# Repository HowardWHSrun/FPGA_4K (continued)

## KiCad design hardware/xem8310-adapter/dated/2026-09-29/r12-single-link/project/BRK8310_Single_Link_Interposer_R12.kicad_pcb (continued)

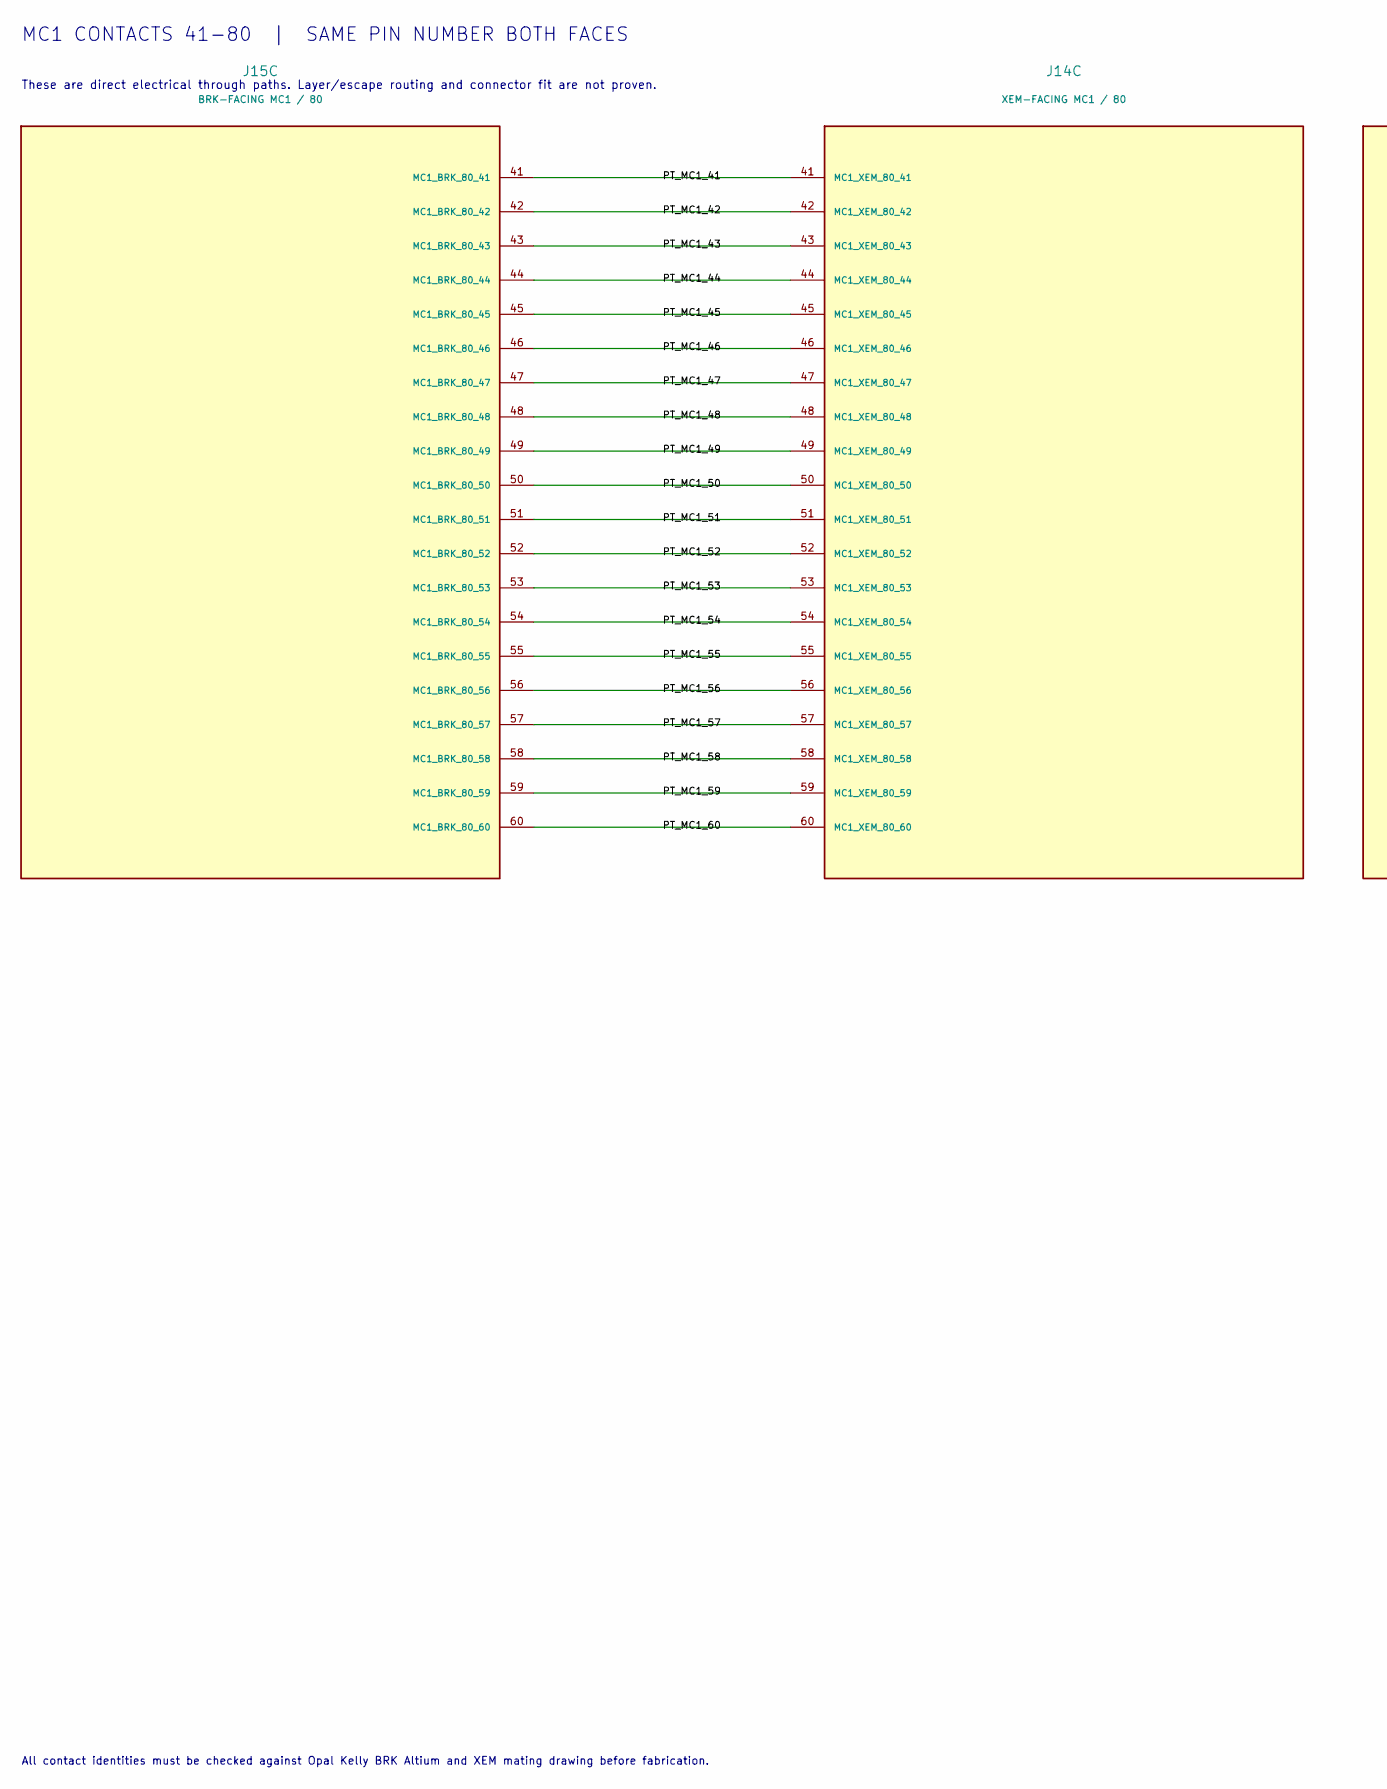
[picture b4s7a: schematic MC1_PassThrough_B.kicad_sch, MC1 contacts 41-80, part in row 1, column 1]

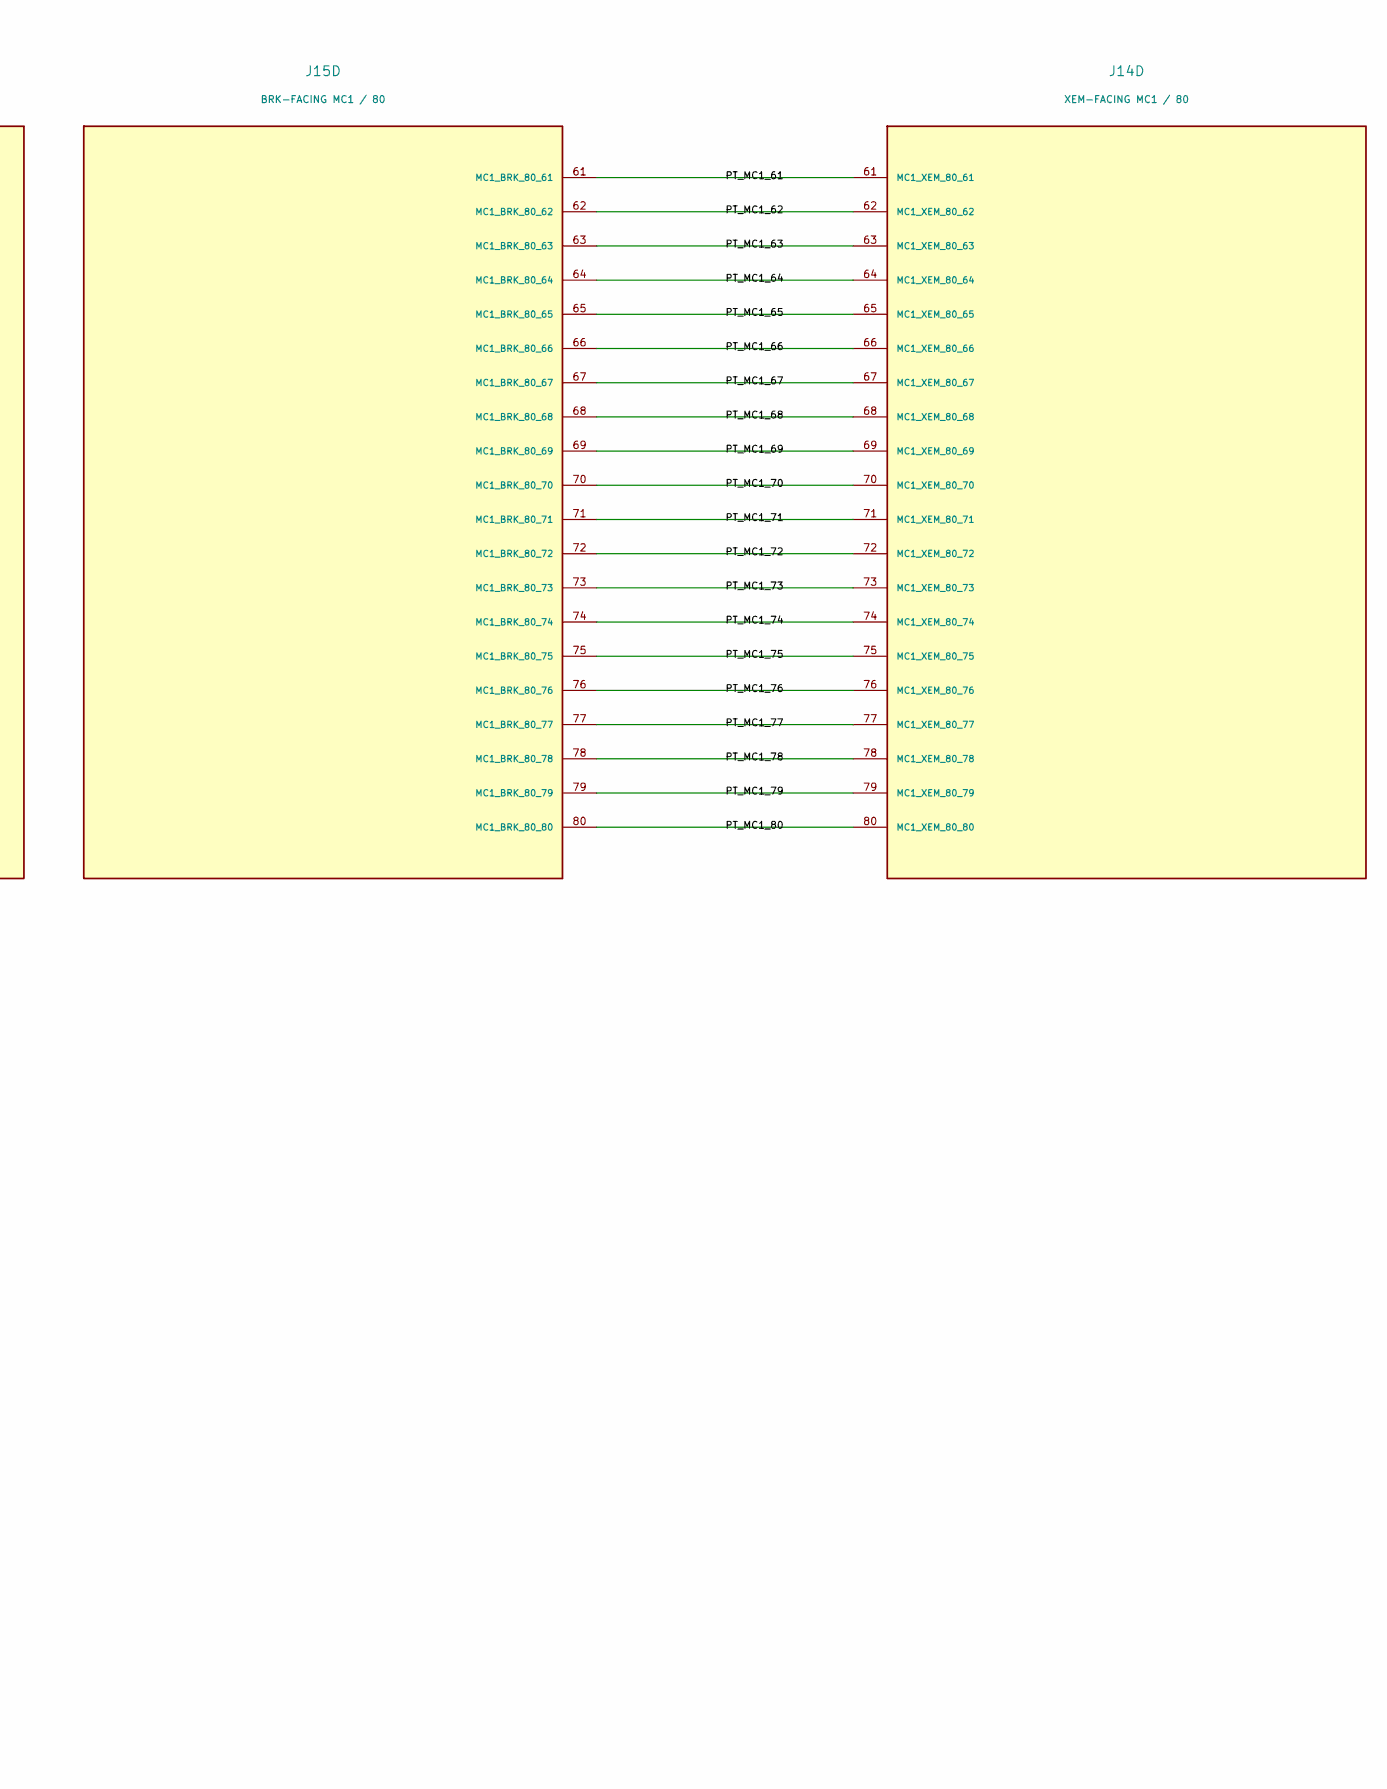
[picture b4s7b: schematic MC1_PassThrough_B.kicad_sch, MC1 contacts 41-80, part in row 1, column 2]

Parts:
J14: XEM-FACING MC1 / 80; BTE_040_01_Top_OpalKelly
J15: BRK-FACING MC1 / 80; BSE_040_01_Bottom_SamtecDrawing

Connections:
/07 / MC1 41-80 PASS-THROUGH/PT_MC1_41: J14.41 (MC1_XEM_80_41), J15.41 (MC1_BRK_80_41)
/07 / MC1 41-80 PASS-THROUGH/PT_MC1_42: J14.42 (MC1_XEM_80_42), J15.42 (MC1_BRK_80_42)
/07 / MC1 41-80 PASS-THROUGH/PT_MC1_43: J14.43 (MC1_XEM_80_43), J15.43 (MC1_BRK_80_43)
/07 / MC1 41-80 PASS-THROUGH/PT_MC1_44: J14.44 (MC1_XEM_80_44), J15.44 (MC1_BRK_80_44)
/07 / MC1 41-80 PASS-THROUGH/PT_MC1_45: J14.45 (MC1_XEM_80_45), J15.45 (MC1_BRK_80_45)
/07 / MC1 41-80 PASS-THROUGH/PT_MC1_46: J14.46 (MC1_XEM_80_46), J15.46 (MC1_BRK_80_46)
/07 / MC1 41-80 PASS-THROUGH/PT_MC1_47: J14.47 (MC1_XEM_80_47), J15.47 (MC1_BRK_80_47)
/07 / MC1 41-80 PASS-THROUGH/PT_MC1_48: J14.48 (MC1_XEM_80_48), J15.48 (MC1_BRK_80_48)
/07 / MC1 41-80 PASS-THROUGH/PT_MC1_49: J14.49 (MC1_XEM_80_49), J15.49 (MC1_BRK_80_49)
/07 / MC1 41-80 PASS-THROUGH/PT_MC1_50: J14.50 (MC1_XEM_80_50), J15.50 (MC1_BRK_80_50)
/07 / MC1 41-80 PASS-THROUGH/PT_MC1_51: J14.51 (MC1_XEM_80_51), J15.51 (MC1_BRK_80_51)
/07 / MC1 41-80 PASS-THROUGH/PT_MC1_52: J14.52 (MC1_XEM_80_52), J15.52 (MC1_BRK_80_52)
/07 / MC1 41-80 PASS-THROUGH/PT_MC1_53: J14.53 (MC1_XEM_80_53), J15.53 (MC1_BRK_80_53)
/07 / MC1 41-80 PASS-THROUGH/PT_MC1_54: J14.54 (MC1_XEM_80_54), J15.54 (MC1_BRK_80_54)
/07 / MC1 41-80 PASS-THROUGH/PT_MC1_55: J14.55 (MC1_XEM_80_55), J15.55 (MC1_BRK_80_55)
/07 / MC1 41-80 PASS-THROUGH/PT_MC1_56: J14.56 (MC1_XEM_80_56), J15.56 (MC1_BRK_80_56)
/07 / MC1 41-80 PASS-THROUGH/PT_MC1_57: J14.57 (MC1_XEM_80_57), J15.57 (MC1_BRK_80_57)
/07 / MC1 41-80 PASS-THROUGH/PT_MC1_58: J14.58 (MC1_XEM_80_58), J15.58 (MC1_BRK_80_58)
/07 / MC1 41-80 PASS-THROUGH/PT_MC1_59: J14.59 (MC1_XEM_80_59), J15.59 (MC1_BRK_80_59)
/07 / MC1 41-80 PASS-THROUGH/PT_MC1_60: J14.60 (MC1_XEM_80_60), J15.60 (MC1_BRK_80_60)
/07 / MC1 41-80 PASS-THROUGH/PT_MC1_61: J14.61 (MC1_XEM_80_61), J15.61 (MC1_BRK_80_61)
/07 / MC1 41-80 PASS-THROUGH/PT_MC1_62: J14.62 (MC1_XEM_80_62), J15.62 (MC1_BRK_80_62)
/07 / MC1 41-80 PASS-THROUGH/PT_MC1_63: J14.63 (MC1_XEM_80_63), J15.63 (MC1_BRK_80_63)
/07 / MC1 41-80 PASS-THROUGH/PT_MC1_64: J14.64 (MC1_XEM_80_64), J15.64 (MC1_BRK_80_64)
/07 / MC1 41-80 PASS-THROUGH/PT_MC1_65: J14.65 (MC1_XEM_80_65), J15.65 (MC1_BRK_80_65)
/07 / MC1 41-80 PASS-THROUGH/PT_MC1_66: J14.66 (MC1_XEM_80_66), J15.66 (MC1_BRK_80_66)
/07 / MC1 41-80 PASS-THROUGH/PT_MC1_67: J14.67 (MC1_XEM_80_67), J15.67 (MC1_BRK_80_67)
/07 / MC1 41-80 PASS-THROUGH/PT_MC1_68: J14.68 (MC1_XEM_80_68), J15.68 (MC1_BRK_80_68)
/07 / MC1 41-80 PASS-THROUGH/PT_MC1_69: J14.69 (MC1_XEM_80_69), J15.69 (MC1_BRK_80_69)
/07 / MC1 41-80 PASS-THROUGH/PT_MC1_70: J14.70 (MC1_XEM_80_70), J15.70 (MC1_BRK_80_70)
/07 / MC1 41-80 PASS-THROUGH/PT_MC1_71: J14.71 (MC1_XEM_80_71), J15.71 (MC1_BRK_80_71)
/07 / MC1 41-80 PASS-THROUGH/PT_MC1_72: J14.72 (MC1_XEM_80_72), J15.72 (MC1_BRK_80_72)
/07 / MC1 41-80 PASS-THROUGH/PT_MC1_73: J14.73 (MC1_XEM_80_73), J15.73 (MC1_BRK_80_73)
/07 / MC1 41-80 PASS-THROUGH/PT_MC1_74: J14.74 (MC1_XEM_80_74), J15.74 (MC1_BRK_80_74)
/07 / MC1 41-80 PASS-THROUGH/PT_MC1_75: J14.75 (MC1_XEM_80_75), J15.75 (MC1_BRK_80_75)
/07 / MC1 41-80 PASS-THROUGH/PT_MC1_76: J14.76 (MC1_XEM_80_76), J15.76 (MC1_BRK_80_76)
/07 / MC1 41-80 PASS-THROUGH/PT_MC1_77: J14.77 (MC1_XEM_80_77), J15.77 (MC1_BRK_80_77)
/07 / MC1 41-80 PASS-THROUGH/PT_MC1_78: J14.78 (MC1_XEM_80_78), J15.78 (MC1_BRK_80_78)
/07 / MC1 41-80 PASS-THROUGH/PT_MC1_79: J14.79 (MC1_XEM_80_79), J15.79 (MC1_BRK_80_79)
/07 / MC1 41-80 PASS-THROUGH/PT_MC1_80: J14.80 (MC1_XEM_80_80), J15.80 (MC1_BRK_80_80)

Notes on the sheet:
MC1 CONTACTS 41-80 | SAME PIN NUMBER BOTH FACES
These are direct electrical through paths. Layer/escape routing and connector fit are not proven.
All contact identities must be checked against Opal Kelly BRK Altium and XEM mating drawing before fabrication.

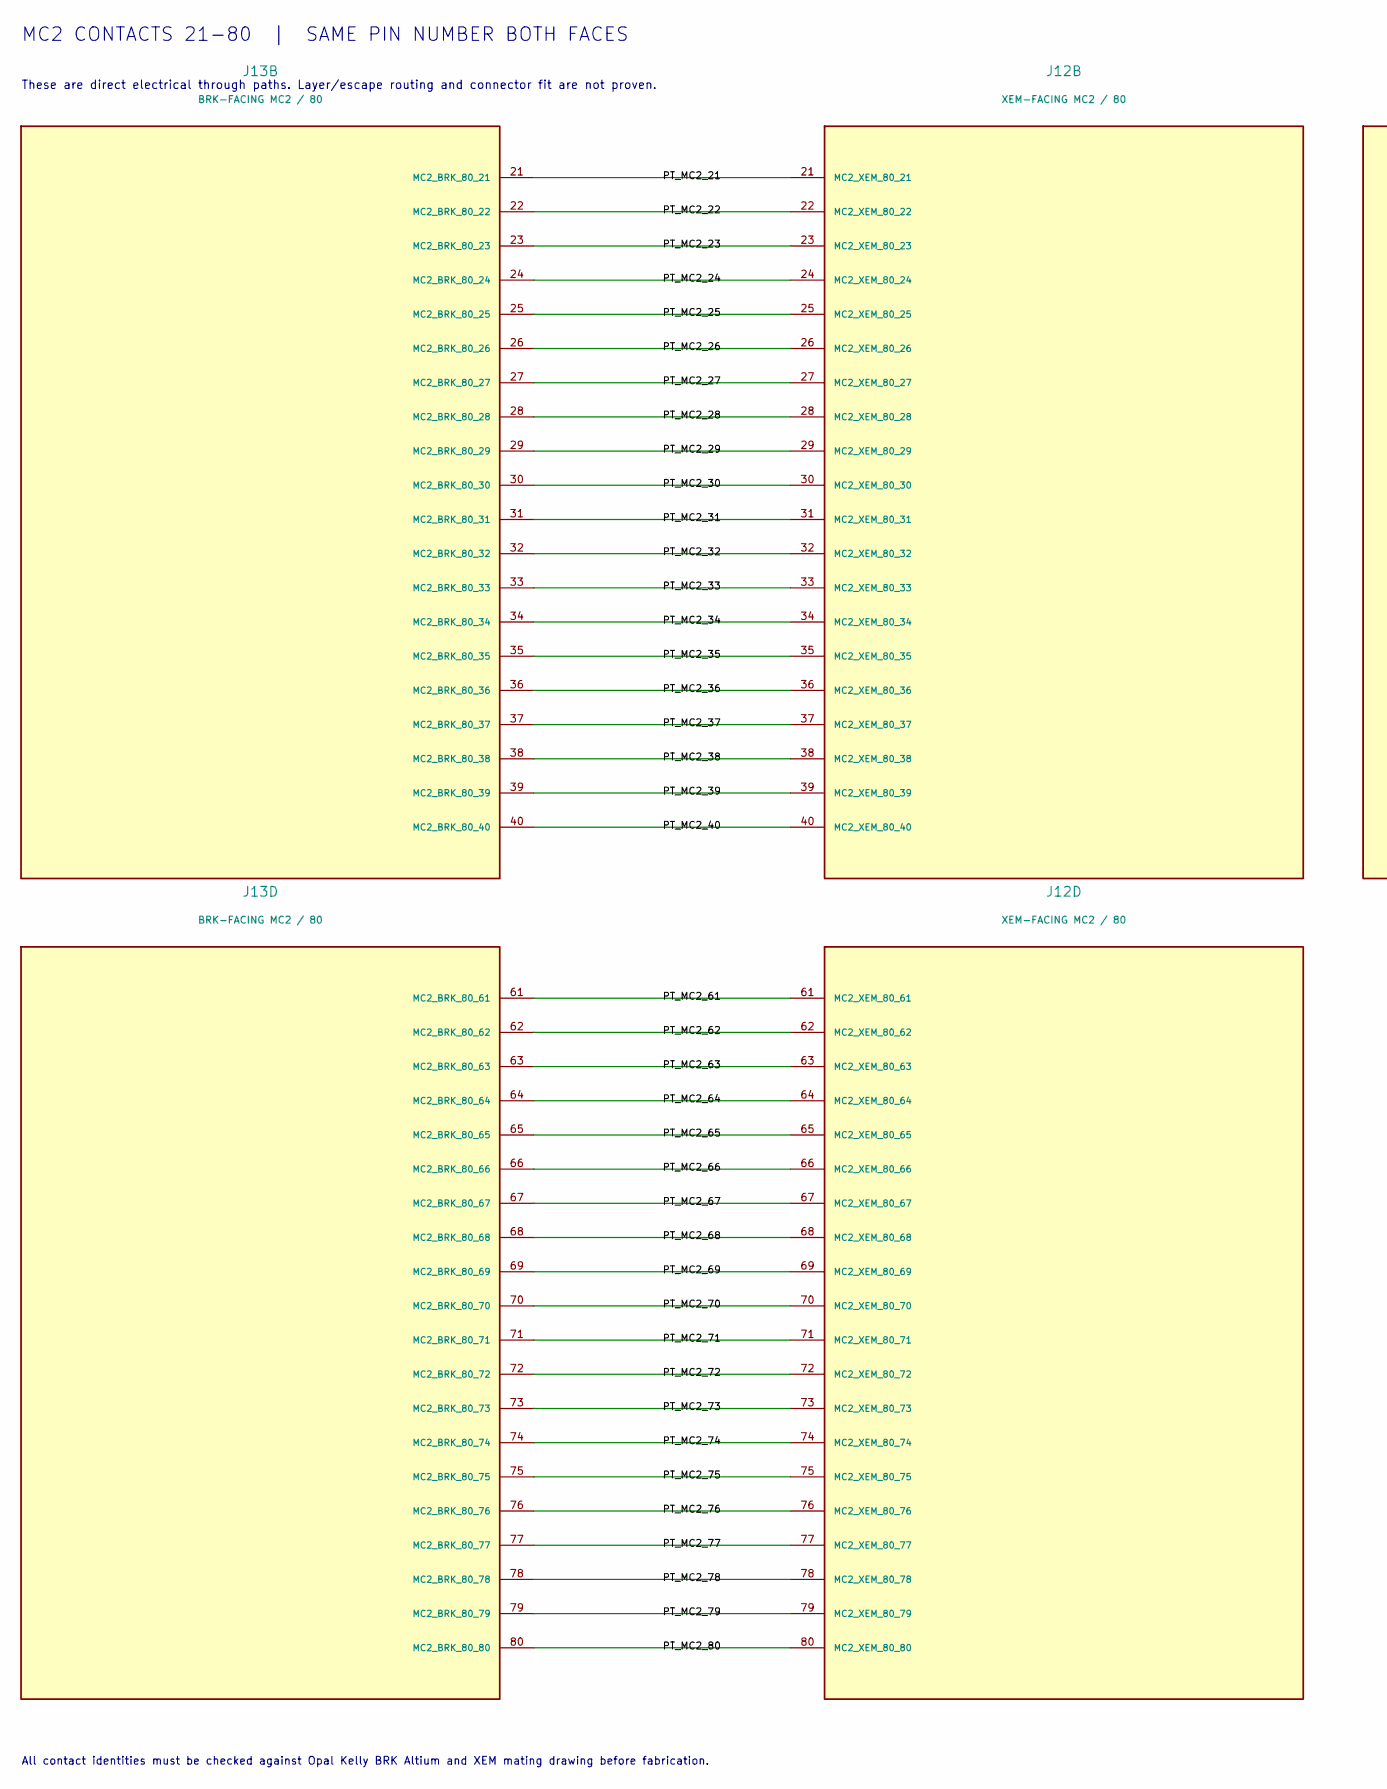
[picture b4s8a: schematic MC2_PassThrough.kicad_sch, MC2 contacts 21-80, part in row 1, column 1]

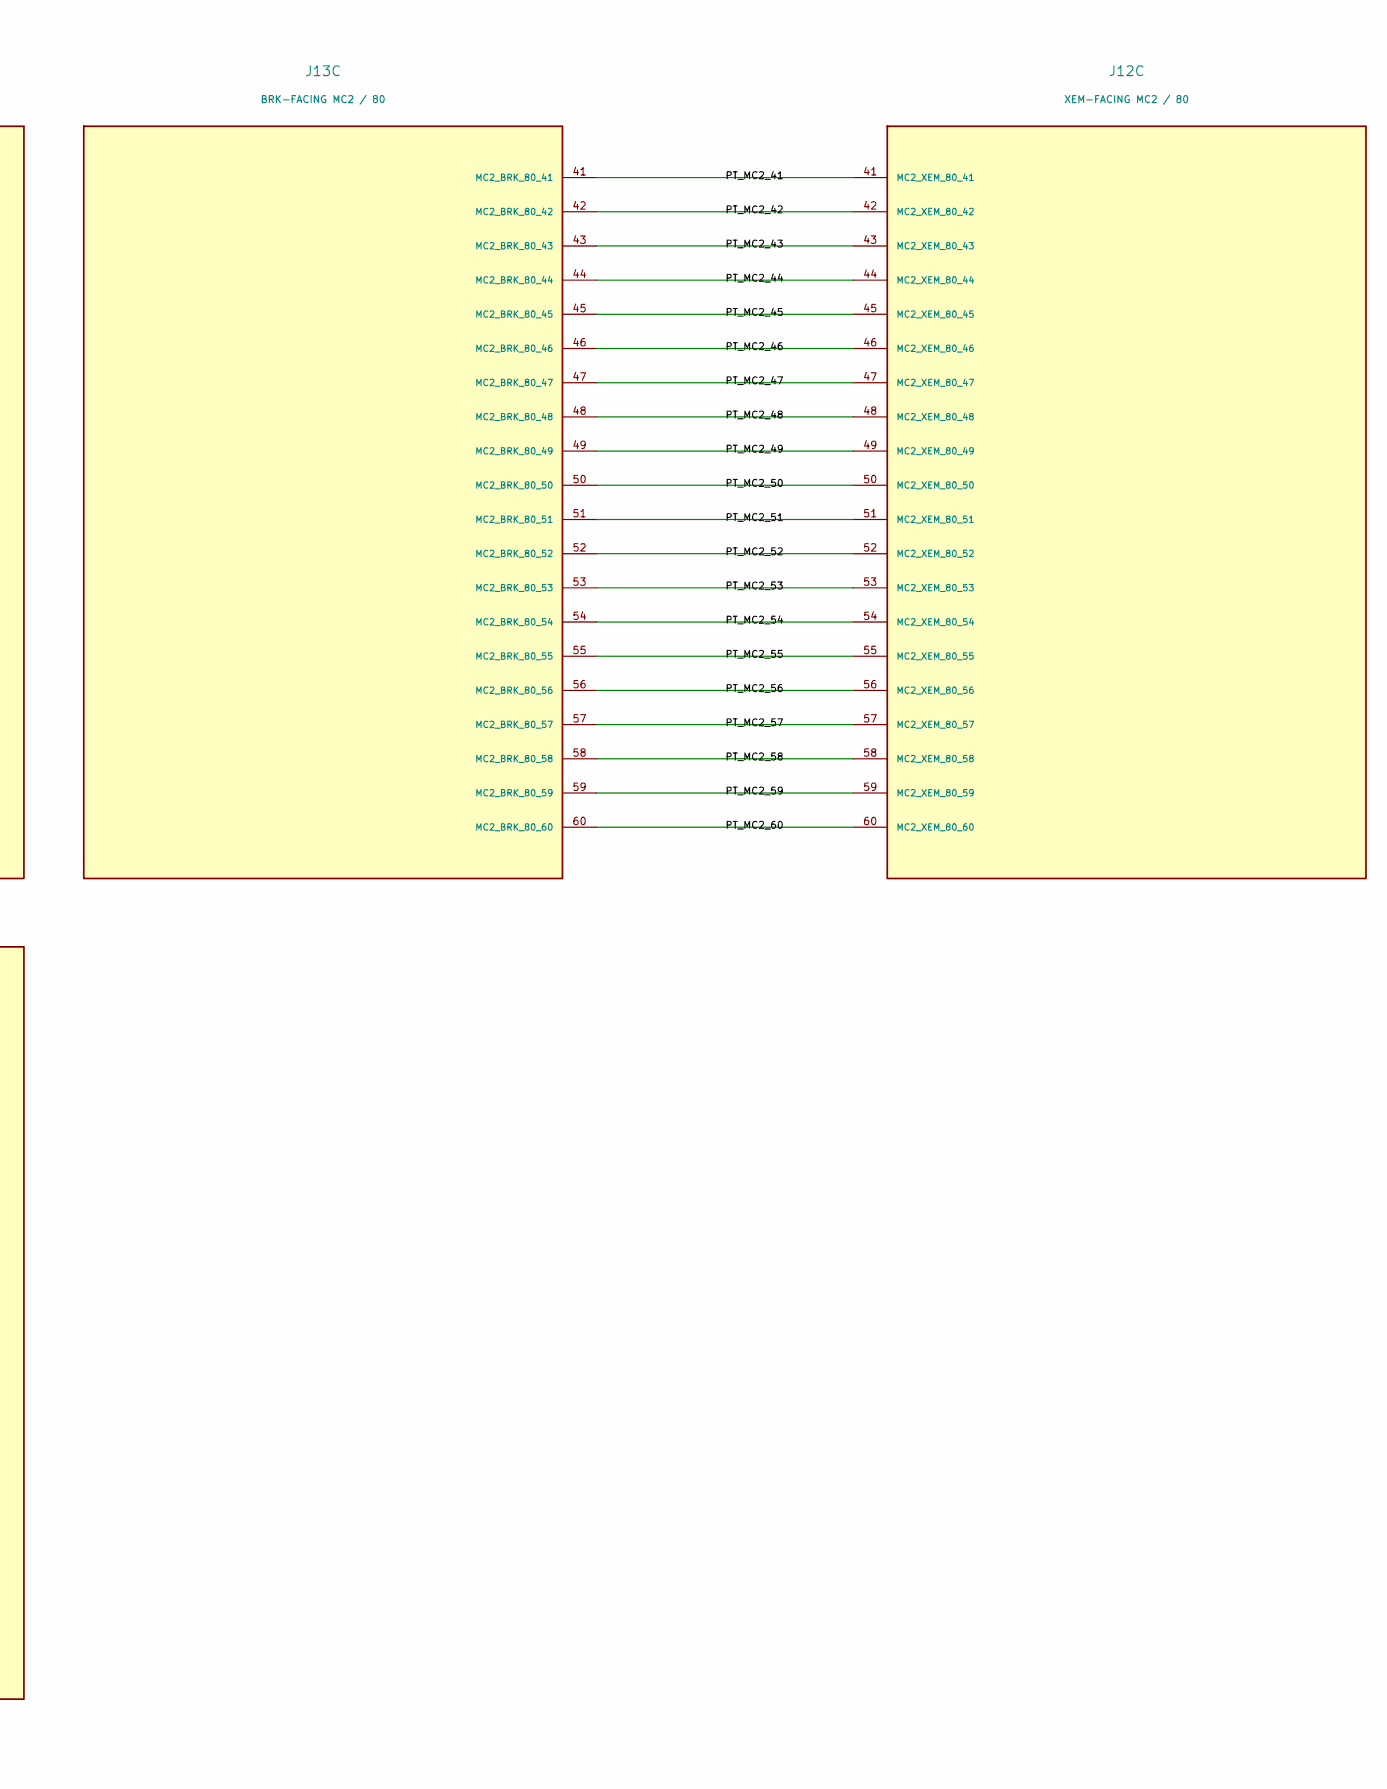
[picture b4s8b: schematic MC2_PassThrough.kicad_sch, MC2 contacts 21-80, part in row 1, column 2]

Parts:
J12: XEM-FACING MC2 / 80; BTE_040_01_Top_OpalKelly
J13: BRK-FACING MC2 / 80; BSE_040_01_Bottom_SamtecDrawing

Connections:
/08 / MC2 21-80 PASS-THROUGH/PT_MC2_21: J12.21 (MC2_XEM_80_21), J13.21 (MC2_BRK_80_21)
/08 / MC2 21-80 PASS-THROUGH/PT_MC2_22: J12.22 (MC2_XEM_80_22), J13.22 (MC2_BRK_80_22)
/08 / MC2 21-80 PASS-THROUGH/PT_MC2_23: J12.23 (MC2_XEM_80_23), J13.23 (MC2_BRK_80_23)
/08 / MC2 21-80 PASS-THROUGH/PT_MC2_24: J12.24 (MC2_XEM_80_24), J13.24 (MC2_BRK_80_24)
/08 / MC2 21-80 PASS-THROUGH/PT_MC2_25: J12.25 (MC2_XEM_80_25), J13.25 (MC2_BRK_80_25)
/08 / MC2 21-80 PASS-THROUGH/PT_MC2_26: J12.26 (MC2_XEM_80_26), J13.26 (MC2_BRK_80_26)
/08 / MC2 21-80 PASS-THROUGH/PT_MC2_27: J12.27 (MC2_XEM_80_27), J13.27 (MC2_BRK_80_27)
/08 / MC2 21-80 PASS-THROUGH/PT_MC2_28: J12.28 (MC2_XEM_80_28), J13.28 (MC2_BRK_80_28)
/08 / MC2 21-80 PASS-THROUGH/PT_MC2_29: J12.29 (MC2_XEM_80_29), J13.29 (MC2_BRK_80_29)
/08 / MC2 21-80 PASS-THROUGH/PT_MC2_30: J12.30 (MC2_XEM_80_30), J13.30 (MC2_BRK_80_30)
/08 / MC2 21-80 PASS-THROUGH/PT_MC2_31: J12.31 (MC2_XEM_80_31), J13.31 (MC2_BRK_80_31)
/08 / MC2 21-80 PASS-THROUGH/PT_MC2_32: J12.32 (MC2_XEM_80_32), J13.32 (MC2_BRK_80_32)
/08 / MC2 21-80 PASS-THROUGH/PT_MC2_33: J12.33 (MC2_XEM_80_33), J13.33 (MC2_BRK_80_33)
/08 / MC2 21-80 PASS-THROUGH/PT_MC2_34: J12.34 (MC2_XEM_80_34), J13.34 (MC2_BRK_80_34)
/08 / MC2 21-80 PASS-THROUGH/PT_MC2_35: J12.35 (MC2_XEM_80_35), J13.35 (MC2_BRK_80_35)
/08 / MC2 21-80 PASS-THROUGH/PT_MC2_36: J12.36 (MC2_XEM_80_36), J13.36 (MC2_BRK_80_36)
/08 / MC2 21-80 PASS-THROUGH/PT_MC2_37: J12.37 (MC2_XEM_80_37), J13.37 (MC2_BRK_80_37)
/08 / MC2 21-80 PASS-THROUGH/PT_MC2_38: J12.38 (MC2_XEM_80_38), J13.38 (MC2_BRK_80_38)
/08 / MC2 21-80 PASS-THROUGH/PT_MC2_39: J12.39 (MC2_XEM_80_39), J13.39 (MC2_BRK_80_39)
/08 / MC2 21-80 PASS-THROUGH/PT_MC2_40: J12.40 (MC2_XEM_80_40), J13.40 (MC2_BRK_80_40)
/08 / MC2 21-80 PASS-THROUGH/PT_MC2_41: J12.41 (MC2_XEM_80_41), J13.41 (MC2_BRK_80_41)
/08 / MC2 21-80 PASS-THROUGH/PT_MC2_42: J12.42 (MC2_XEM_80_42), J13.42 (MC2_BRK_80_42)
/08 / MC2 21-80 PASS-THROUGH/PT_MC2_43: J12.43 (MC2_XEM_80_43), J13.43 (MC2_BRK_80_43)
/08 / MC2 21-80 PASS-THROUGH/PT_MC2_44: J12.44 (MC2_XEM_80_44), J13.44 (MC2_BRK_80_44)
/08 / MC2 21-80 PASS-THROUGH/PT_MC2_45: J12.45 (MC2_XEM_80_45), J13.45 (MC2_BRK_80_45)
/08 / MC2 21-80 PASS-THROUGH/PT_MC2_46: J12.46 (MC2_XEM_80_46), J13.46 (MC2_BRK_80_46)
/08 / MC2 21-80 PASS-THROUGH/PT_MC2_47: J12.47 (MC2_XEM_80_47), J13.47 (MC2_BRK_80_47)
/08 / MC2 21-80 PASS-THROUGH/PT_MC2_48: J12.48 (MC2_XEM_80_48), J13.48 (MC2_BRK_80_48)
/08 / MC2 21-80 PASS-THROUGH/PT_MC2_49: J12.49 (MC2_XEM_80_49), J13.49 (MC2_BRK_80_49)
/08 / MC2 21-80 PASS-THROUGH/PT_MC2_50: J12.50 (MC2_XEM_80_50), J13.50 (MC2_BRK_80_50)
/08 / MC2 21-80 PASS-THROUGH/PT_MC2_51: J12.51 (MC2_XEM_80_51), J13.51 (MC2_BRK_80_51)
/08 / MC2 21-80 PASS-THROUGH/PT_MC2_52: J12.52 (MC2_XEM_80_52), J13.52 (MC2_BRK_80_52)
/08 / MC2 21-80 PASS-THROUGH/PT_MC2_53: J12.53 (MC2_XEM_80_53), J13.53 (MC2_BRK_80_53)
/08 / MC2 21-80 PASS-THROUGH/PT_MC2_54: J12.54 (MC2_XEM_80_54), J13.54 (MC2_BRK_80_54)
/08 / MC2 21-80 PASS-THROUGH/PT_MC2_55: J12.55 (MC2_XEM_80_55), J13.55 (MC2_BRK_80_55)
/08 / MC2 21-80 PASS-THROUGH/PT_MC2_56: J12.56 (MC2_XEM_80_56), J13.56 (MC2_BRK_80_56)
/08 / MC2 21-80 PASS-THROUGH/PT_MC2_57: J12.57 (MC2_XEM_80_57), J13.57 (MC2_BRK_80_57)
/08 / MC2 21-80 PASS-THROUGH/PT_MC2_58: J12.58 (MC2_XEM_80_58), J13.58 (MC2_BRK_80_58)
/08 / MC2 21-80 PASS-THROUGH/PT_MC2_59: J12.59 (MC2_XEM_80_59), J13.59 (MC2_BRK_80_59)
/08 / MC2 21-80 PASS-THROUGH/PT_MC2_60: J12.60 (MC2_XEM_80_60), J13.60 (MC2_BRK_80_60)
/08 / MC2 21-80 PASS-THROUGH/PT_MC2_61: J12.61 (MC2_XEM_80_61), J13.61 (MC2_BRK_80_61)
/08 / MC2 21-80 PASS-THROUGH/PT_MC2_62: J12.62 (MC2_XEM_80_62), J13.62 (MC2_BRK_80_62)
/08 / MC2 21-80 PASS-THROUGH/PT_MC2_63: J12.63 (MC2_XEM_80_63), J13.63 (MC2_BRK_80_63)
/08 / MC2 21-80 PASS-THROUGH/PT_MC2_64: J12.64 (MC2_XEM_80_64), J13.64 (MC2_BRK_80_64)
/08 / MC2 21-80 PASS-THROUGH/PT_MC2_65: J12.65 (MC2_XEM_80_65), J13.65 (MC2_BRK_80_65)
/08 / MC2 21-80 PASS-THROUGH/PT_MC2_66: J12.66 (MC2_XEM_80_66), J13.66 (MC2_BRK_80_66)
/08 / MC2 21-80 PASS-THROUGH/PT_MC2_67: J12.67 (MC2_XEM_80_67), J13.67 (MC2_BRK_80_67)
/08 / MC2 21-80 PASS-THROUGH/PT_MC2_68: J12.68 (MC2_XEM_80_68), J13.68 (MC2_BRK_80_68)
/08 / MC2 21-80 PASS-THROUGH/PT_MC2_69: J12.69 (MC2_XEM_80_69), J13.69 (MC2_BRK_80_69)
/08 / MC2 21-80 PASS-THROUGH/PT_MC2_70: J12.70 (MC2_XEM_80_70), J13.70 (MC2_BRK_80_70)
/08 / MC2 21-80 PASS-THROUGH/PT_MC2_71: J12.71 (MC2_XEM_80_71), J13.71 (MC2_BRK_80_71)
/08 / MC2 21-80 PASS-THROUGH/PT_MC2_72: J12.72 (MC2_XEM_80_72), J13.72 (MC2_BRK_80_72)
/08 / MC2 21-80 PASS-THROUGH/PT_MC2_73: J12.73 (MC2_XEM_80_73), J13.73 (MC2_BRK_80_73)
/08 / MC2 21-80 PASS-THROUGH/PT_MC2_74: J12.74 (MC2_XEM_80_74), J13.74 (MC2_BRK_80_74)
/08 / MC2 21-80 PASS-THROUGH/PT_MC2_75: J12.75 (MC2_XEM_80_75), J13.75 (MC2_BRK_80_75)
/08 / MC2 21-80 PASS-THROUGH/PT_MC2_76: J12.76 (MC2_XEM_80_76), J13.76 (MC2_BRK_80_76)
/08 / MC2 21-80 PASS-THROUGH/PT_MC2_77: J12.77 (MC2_XEM_80_77), J13.77 (MC2_BRK_80_77)
/08 / MC2 21-80 PASS-THROUGH/PT_MC2_78: J12.78 (MC2_XEM_80_78), J13.78 (MC2_BRK_80_78)
/08 / MC2 21-80 PASS-THROUGH/PT_MC2_79: J12.79 (MC2_XEM_80_79), J13.79 (MC2_BRK_80_79)
/08 / MC2 21-80 PASS-THROUGH/PT_MC2_80: J12.80 (MC2_XEM_80_80), J13.80 (MC2_BRK_80_80)

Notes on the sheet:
MC2 CONTACTS 21-80 | SAME PIN NUMBER BOTH FACES
These are direct electrical through paths. Layer/escape routing and connector fit are not proven.
All contact identities must be checked against Opal Kelly BRK Altium and XEM mating drawing before fabrication.

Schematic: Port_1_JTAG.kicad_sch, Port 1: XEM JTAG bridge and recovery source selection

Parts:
C121, C122: 100nF / 16V X7R; C_0603_1608Metric
J21: XILINX 14-PIN / 2.00 mm; PinHeader_2x07_P2.00mm_Vertical
JP121: TMS SOURCE / DEFAULT 2-3; PinHeader_1x03_P1.27mm_Vertical_SMD_Pin1Left
JP122: TDI SOURCE / DEFAULT 2-3; PinHeader_1x03_P1.27mm_Vertical_SMD_Pin1Left
JP123: TCK SOURCE / DEFAULT 2-3; PinHeader_1x03_P1.27mm_Vertical_SMD_Pin1Left
JP124: XEM ARM / DEFAULT OPEN; PinHeader_1x02_P1.27mm_Vertical_SMD_Pin1Left
R121, R122, R123: 33R / source damping; R_0603_1608Metric
R124: 10k / target TMS pull-up; R_0603_1608Metric
R125: 10k / target TDI pull-up; R_0603_1608Metric
R126: 10k / target TCK pull-down; R_0603_1608Metric
R127: 10k / A-side TMS idle high; R_0603_1608Metric
R128: 10k / A-side TDI idle high; R_0603_1608Metric
R129: 10k / A-side TCK idle low; R_0603_1608Metric
R130: 10k / default disabled; R_0603_1608Metric
R131: 100k / TDO idle low; R_0603_1608Metric
U101: SN74AXC4T774PWR; TSSOP-16_4.4x5mm_P0.65mm

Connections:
P1_BRIDGE_OE_N: JP124.2 (EN_INPUT), R130.1, U101.9 (OE_N)
P1_PROBE_TCK: J21.6 (TCK), JP123.3 (PROBE)
P1_PROBE_TDI: J21.10 (TDI), JP122.3 (PROBE)
P1_PROBE_TMS: J21.4 (TMS), JP121.3 (PROBE)
P1_TCK: JP123.2 (TARGET), R126.1; also elsewhere on the board
P1_TDI: JP122.2 (TARGET), R125.1; also elsewhere on the board
P1_TDO: J21.8 (TDO), R131.1, U101.11 (B4_TDO); also elsewhere on the board
P1_TMS: JP121.2 (TARGET), R124.1; also elsewhere on the board
P1_VTREF_1V8_TARGET: C122.1, J21.2 (VTREF_TARGET), R124.2, R125.2, U101.15 (VCCB_TARGET_VTREF); also elsewhere on the board
P1_XEM_OE_N: JP124.1 (SOURCE); also elsewhere on the board
P1_XEM_TCK: R129.1, U101.5 (A3_TCK); also elsewhere on the board
P1_XEM_TCK_1V8: JP123.1 (XEM), R123.2
P1_XEM_TCK_1V8_RAW: R123.1, U101.12 (B3_TCK)
P1_XEM_TDI: R128.1, U101.4 (A2_TDI); also elsewhere on the board
P1_XEM_TDI_1V8: JP122.1 (XEM), R122.2
P1_XEM_TDI_1V8_RAW: R122.1, U101.13 (B2_TDI)
P1_XEM_TDO: U101.6 (A4_TDO); also elsewhere on the board
P1_XEM_TMS: R127.1, U101.3 (A1_TMS); also elsewhere on the board
P1_XEM_TMS_1V8: JP121.1 (XEM), R121.2
P1_XEM_TMS_1V8_RAW: R121.1, U101.14 (B1_TMS)
SYS_GND: C121.2, C122.2, J21.1 (GND), J21.3 (GND), J21.5 (GND), J21.7 (GND), J21.9 (GND), J21.11 (GND), J21.13 (GND), R126.2, R129.2, R131.2, U101.8 (DIR4), U101.10 (GND); also elsewhere on the board
XEM_1V2_DDR: C121.1, R127.2, R128.2, R130.2, U101.1 (DIR1), U101.2 (DIR2), U101.7 (DIR3), U101.16 (VCCA_1V2); also elsewhere on the board

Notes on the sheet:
PORT 1 | INDEPENDENT 1.2 V / TARGET 1.8 V JTAG
Target-derived VTREF supplies the translator B rail; the host never drives VTREF. The host does not supply the target reference.
Default: all three source shunts 2-3 PROBE; ARM jumper open. Move all three to 1-2 for XEM master operation.
DIR1/2/3 = HIGH: TMS/TDI/TCK to target. DIR4 = LOW: target TDO to XEM. /OE defaults HIGH.
MC3.80 is +1.2V_DDR (250 mA shared user budget). Target pin 1 bias/inrush load, signal timing and gateware require review.

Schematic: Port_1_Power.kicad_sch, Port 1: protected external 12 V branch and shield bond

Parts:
C311: 1uF / 50V X7R input; C_0805_2012Metric
C312: 100nF / 50V X7R input; C_0805_2012Metric
C313: 2.2uF / 50V X7R output; C_0805_2012Metric
C314: 4.7nF / 50V C0G / ~28ms; C_0603_1608Metric
D300: SMBJ15CA / common-input candidate; D_SMB
D301: PMEG3050EPX / negative clamp; D_SOD-128
JP311: 12 V ARM / DEFAULT OPEN; PinHeader_1x02_P1.27mm_Vertical_SMD_Pin1Left
R132: 0R / shield bond review option; R_0603_1608Metric
R311: 750k 1% / UVLO top; R_0603_1608Metric
R312: 100k 1% / UVLO bottom; R_0603_1608Metric
R313: 1M 1% / OVLO top; R_0603_1608Metric
R314: 90.9k 1% / OVLO bottom; R_0603_1608Metric
R315: 6.49k 1% / ~0.51 A nominal; R_0603_1608Metric
TP301: FLT_N / open drain / no pull-up; TestPoint_Pad_D1.0mm
U301: TPS259470LRPWR / latch-off; TI_RPW0010A_TPS25947

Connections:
P1_EFUSE_DVDT: C314.1, U301.7 (DVDT)
P1_EFUSE_EN: R311.2, R312.1, U301.1 (EN_UVLO)
P1_EFUSE_EN_FEED: JP311.2 (EN_INPUT), R311.1
P1_EFUSE_FLT_N: TP301.1, U301.4 (FLT_N_OPEN_DRAIN)
P1_EFUSE_ILM: R315.1, U301.9 (ILM)
P1_EFUSE_OVLO: R313.2, R314.1, U301.2 (OVLO)
P1_LINK_12V: C313.1, D301.1 (K), U301.6 (OUT); also elsewhere on the board
P1_SHIELD: R132.1; also elsewhere on the board
SYS_GND: C311.2, C312.2, C313.2, C314.2, D300.2, D301.2 (A), R132.2, R312.2, R314.2, R315.2, U301.8 (GND); also elsewhere on the board
VDCIN_EXTERNAL_12V_CANDIDATE: C311.1, C312.1, D300.1, JP311.1 (SOURCE), R313.1, U301.5 (IN); also elsewhere on the board

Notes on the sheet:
PORT 1 | PROTECTED 12 V TO CONTACT 19
A latch-off eFuse protects the single cable. Enable shunt is open by default; install only after the remote load is reviewed.
Approx. 0.51 A nominal is an adjustable study setting, not a qualified cable limit or a proven FPGA/ASIC power budget.
Five cable GND contacts carry return current. Shell bonds through 0R; shell is not the only load return.
UVLO approx.10.2 V; OVLO approx.14.4 V. ITIMER/AUXOFF NC; FLT_N has no host-voltage pull-up.
Use a clean regulated 12 V source. Shared SMBJ15CA does not limit the XEM input to its 15 V operating maximum.

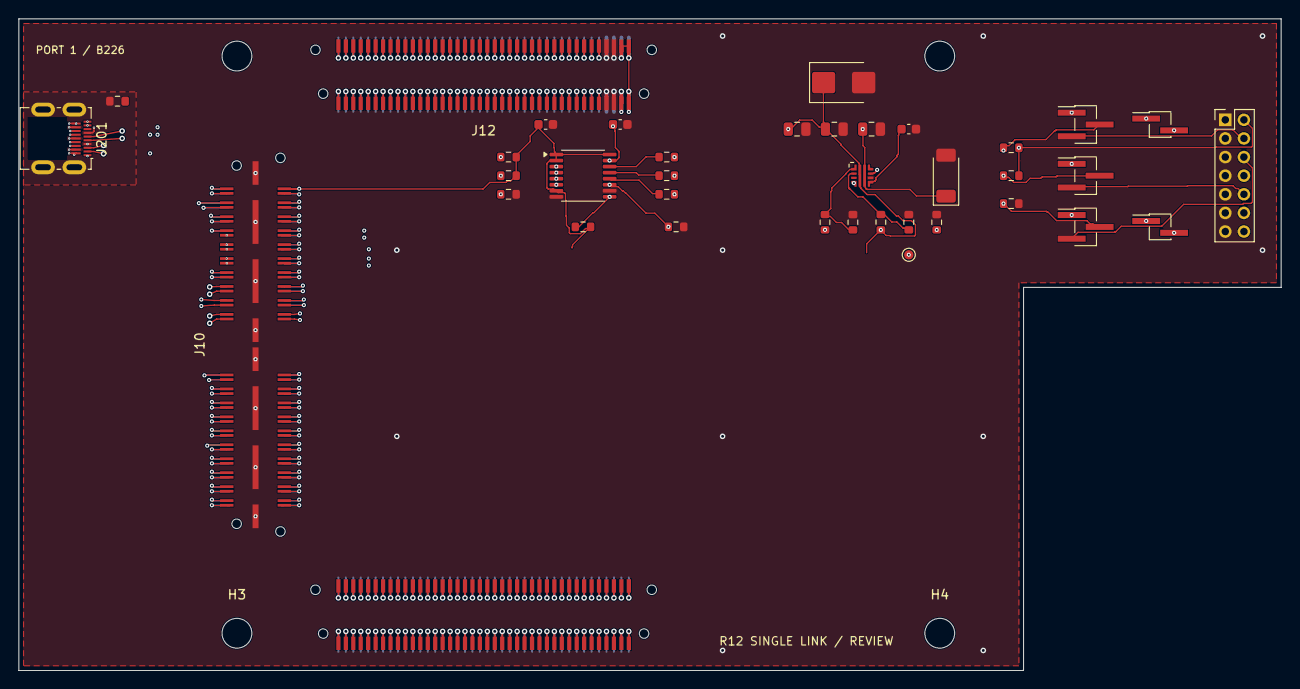
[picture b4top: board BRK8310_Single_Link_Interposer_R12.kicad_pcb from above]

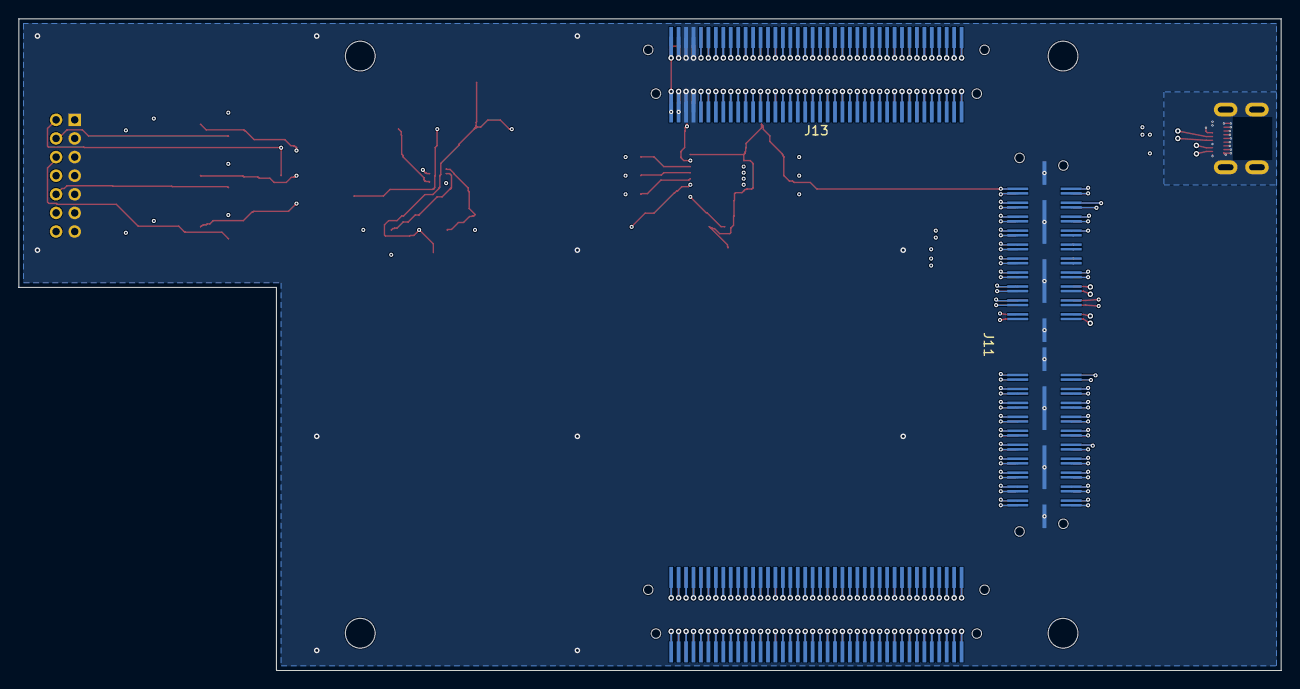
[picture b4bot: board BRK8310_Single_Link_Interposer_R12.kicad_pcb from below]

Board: 8 copper layers, 135.6 x 70.0 mm, 45 parts (3 on the bottom side), 257 nets.

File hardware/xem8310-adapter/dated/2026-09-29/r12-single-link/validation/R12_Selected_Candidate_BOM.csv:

Reference,Value,Footprint,Datasheet,Status
C121,100nF / 16V X7R,Capacitor_SMD:C_0603_1608Metric,,R12 study; not fabrication qualified
C122,100nF / 16V X7R,Capacitor_SMD:C_0603_1608Metric,,R12 study; not fabrication qualified
C311,1uF / 50V X7R input,Capacitor_SMD:C_0805_2012Metric,,R12 study; not fabrication qualified
C312,100nF / 50V X7R input,Capacitor_SMD:C_0805_2012Metric,,R12 study; not fabrication qualified
C313,2.2uF / 50V X7R output,Capacitor_SMD:C_0805_2012Metric,,R12 study; not fabrication qualified
C314,4.7nF / 50V C0G / ~28ms,Capacitor_SMD:C_0603_1608Metric,,R12 study; not fabrication qualified
D300,SMBJ15CA / common-input candidate,Diode_SMD:D_SMB,https://www.littelfuse.com/assetdocs/tvs-diodes-smbj-series-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,R12 study; not fabrication qualified
D301,PMEG3050EPX / negative clamp,Diode_SMD:D_SOD-128,https://assets.nexperia.com/documents/data-sheet/PMEG3050EP.pdf,R12 study; not fabrication qualified
J10,XEM-FACING MC3 / 80 CONTACTS,AdapterR8:QTH_040_01_Top_OpalKelly,,R12 study; not fabrication qualified
J11,BRK-FACING MC3 / 80 CONTACTS,AdapterR8:QSH_040_01_Bottom_SamtecDrawing,,R12 study; not fabrication qualified
J12,XEM-FACING MC2 / 80,AdapterR8:BTE_040_01_Top_OpalKelly,,R12 study; not fabrication qualified
J13,BRK-FACING MC2 / 80,AdapterR8:BSE_040_01_Bottom_SamtecDrawing,,R12 study; not fabrication qualified
J14,XEM-FACING MC1 / 80,AdapterR8:BTE_040_01_Top_OpalKelly,,R12 study; not fabrication qualified
J15,BRK-FACING MC1 / 80,AdapterR8:BSE_040_01_Bottom_SamtecDrawing,,R12 study; not fabrication qualified
J201,PORT 1 / CUSTOM TYPE-D,Connector_Video:HDMI_Micro-D_Molex_46765-1xxx,,R12 study; not fabrication qualified
J21,XILINX 14-PIN / 2.00 mm,Connector_PinHeader_2.00mm:PinHeader_2x07_P2.00mm_Vertical,https://docs.amd.com/r/en-US/ug908-vivado-programming-debugg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,R12 study; not fabrication qualified
JP121,TMS SOURCE / DEFAULT 2-3,Connector_PinHeader_1.27mm:PinHeader_1x03_P1.27mm_Vertical_SMD_Pin1Left,,R12 study; not fabrication qualified
JP122,TDI SOURCE / DEFAULT 2-3,Connector_PinHeader_1.27mm:PinHeader_1x03_P1.27mm_Vertical_SMD_Pin1Left,,R12 study; not fabrication qualified
JP123,TCK SOURCE / DEFAULT 2-3,Connector_PinHeader_1.27mm:PinHeader_1x03_P1.27mm_Vertical_SMD_Pin1Left,,R12 study; not fabrication qualified
JP124,XEM ARM / DEFAULT OPEN,Connector_PinHeader_1.27mm:PinHeader_1x02_P1.27mm_Vertical_SMD_Pin1Left,,R12 study; not fabrication qualified
JP311,12 V ARM / DEFAULT OPEN,Connector_PinHeader_1.27mm:PinHeader_1x02_P1.27mm_Vertical_SMD_Pin1Left,,R12 study; not fabrication qualified
R121,33R / source damping,Resistor_SMD:R_0603_1608Metric,,R12 study; not fabrication qualified
R122,33R / source damping,Resistor_SMD:R_0603_1608Metric,,R12 study; not fabrication qualified
R123,33R / source damping,Resistor_SMD:R_0603_1608Metric,,R12 study; not fabrication qualified
R124,10k / target TMS pull-up,Resistor_SMD:R_0603_1608Metric,,R12 study; not fabrication qualified
R125,10k / target TDI pull-up,Resistor_SMD:R_0603_1608Metric,,R12 study; not fabrication qualified
R126,10k / target TCK pull-down,Resistor_SMD:R_0603_1608Metric,,R12 study; not fabrication qualified
R127,10k / A-side TMS idle high,Resistor_SMD:R_0603_1608Metric,,R12 study; not fabrication qualified
R128,10k / A-side TDI idle high,Resistor_SMD:R_0603_1608Metric,,R12 study; not fabrication qualified
R129,10k / A-side TCK idle low,Resistor_SMD:R_0603_1608Metric,,R12 study; not fabrication qualified
R130,10k / default disabled,Resistor_SMD:R_0603_1608Metric,,R12 study; not fabrication qualified
R131,100k / TDO idle low,Resistor_SMD:R_0603_1608Metric,,R12 study; not fabrication qualified
R132,0R / shield bond review option,Resistor_SMD:R_0603_1608Metric,,R12 study; not fabrication qualified
R311,750k 1% / UVLO top,Resistor_SMD:R_0603_1608Metric,,R12 study; not fabrication qualified
R312,100k 1% / UVLO bottom,Resistor_SMD:R_0603_1608Metric,,R12 study; not fabrication qualified
R313,1M 1% / OVLO top,Resistor_SMD:R_0603_1608Metric,,R12 study; not fabrication qualified
R314,90.9k 1% / OVLO bottom,Resistor_SMD:R_0603_1608Metric,,R12 study; not fabrication qualified
R315,6.49k 1% / ~0.51 A nominal,Resistor_SMD:R_0603_1608Metric,,R12 study; not fabrication qualified
TP301,FLT_N / open drain / no pull-up,TestPoint:TestPoint_Pad_D1.0mm,,R12 study; not fabrication qualified
U101,SN74AXC4T774PWR,Package_SO:TSSOP-16_4.4x5mm_P0.65mm,https://www.ti.com/lit/ds/symlink/sn74axc4t774.pdf,R12 study; not fabrication qualified
U301,TPS259470LRPWR / latch-off,AdapterR11:TI_RPW0010A_TPS25947,https://www.ti.com/lit/ds/symlink/tps25947.pdf,R12 study; not fabrication qualified
